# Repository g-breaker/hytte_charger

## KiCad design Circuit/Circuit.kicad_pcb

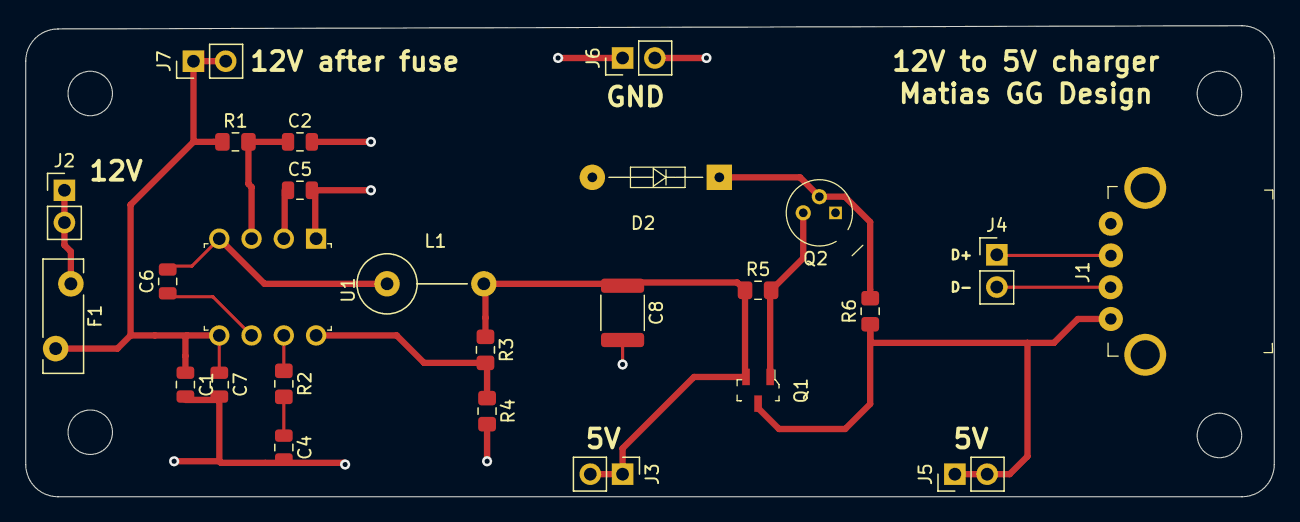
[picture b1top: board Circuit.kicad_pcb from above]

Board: 2 copper layers, 98.3 x 37.1 mm, 30 parts (0 on the bottom side), 16 nets.

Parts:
C1: 220u; C_0805_2012Metric
C2: 2.7n; C_0805_2012Metric
C4: 22n; C_0805_2012Metric
C5, C6, C7: 220n; C_0805_2012Metric
C8: 470u; C_1812_4532Metric
D2: 1N4148; Diode_DO-35_P10mm
F1: Polyfuse; Fuse_Bourns_MF-RHT300
J1: UE27AC54100; USB_A_Female_UE27AC54100
J2, J3, J4, J5, J6, J7: 22-23-2021; PinHeader_1x02_P2.54mm_Vertical
L1: 120u; L_Axial_L11.0mm_D4.5mm_P7.62mm_Vertical_Fastron_MECC
Mnt1, Mnt2, Mnt3, Mnt4: MountingHole_3.5mm
Q1: AO3401A; SOT-23-3
Q2: 2N2222A; TO-18-3
R1: 20k; R_0805_2012Metric_Pad1.15x1.40mm_HandSolder
R2: 9.1k; R_0805_2012Metric_Pad1.15x1.40mm_HandSolder
R3: 1.2k; R_0805_2012Metric_Pad1.15x1.40mm_HandSolder
R4: 2.4k; R_0805_2012Metric_Pad1.15x1.40mm_HandSolder
R5, R6: 10k; R_0805_2012Metric_Pad1.15x1.40mm_HandSolder
U1: L4978; DIP-8_W7.62mm

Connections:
+5V: C8.1, J3.1, J3.2, L1.2, Q1.2, R3.1, R5.1
+12V: F1.1, J2.1, J2.2
/D+: J1.3, J4.1
/D-: J1.2, J4.2
GND: C1.2, C2.2, C4.2, C5.2, C7.2, C8.2, D2.2, J1.4, J6.1, J6.2, Q2.1, R4.2, U1.1
unnamed: C1.1, C7.1, F1.2, J7.1, J7.2, R1.1, U1.5
unnamed: C2.1, R1.2, U1.3
unnamed: C4.1, R2.2
unnamed: C5.1, U1.2
unnamed: C6.1, U1.6
unnamed: C6.2, L1.1, U1.4
unnamed: D2.1, Q2.2, R6.2
unnamed: J1.1, J5.1, J5.2, Q1.3, R6.1
unnamed: Q1.1, Q2.3, R5.2
unnamed: R2.1, U1.7
unnamed: R3.2, R4.1, U1.8

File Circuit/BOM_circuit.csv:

"Id";"Designator";"Package";"Quantity";"Designation";"Supplier and ref";
1;"J7,J5,J6,J4,J3,J2";"PinHeader_1x02_P2.54mm_Vertical";6;"22-23-2021";;;
2;"F1";"Fuse_Bourns_MF-RHT300";1;"Polyfuse";;;
3;"Mnt2,Mnt4,Mnt3,Mnt1";"MountingHole_3.5mm";4;"MountingHole_3.5mm";;;
4;"C8";"C_1812_4532Metric";1;"470u";;;
5;"C7,C6,C5";"C_0805_2012Metric";3;"220n";;;
6;"C4";"C_0805_2012Metric";1;"22n";;;
7;"C2";"C_0805_2012Metric";1;"2.7n";;;
8;"C1";"C_0805_2012Metric";1;"220u";;;
9;"R1";"R_0805_2012Metric_Pad1.15x1.40mm_HandSolder";1;"20k";;;
10;"D2";"Diode_DO-35_P10mm";1;"1N4148";;;
11;"J1";"USB_A_Female_UE27AC54100";1;"UE27AC54100";;;
12;"L1";"L_Axial_L11.0mm_D4.5mm_P7.62mm_Vertical_Fastron_MECC";1;"120u";;;
13;"Q1";"SOT-23-3";1;"AO3401A";;;
14;"Q2";"TO-18-3";1;"2N2222A";;;
15;"R6,R5";"R_0805_2012Metric_Pad1.15x1.40mm_HandSolder";2;"10k";;;
16;"R2";"R_0805_2012Metric_Pad1.15x1.40mm_HandSolder";1;"9.1k";;;
17;"R3";"R_0805_2012Metric_Pad1.15x1.40mm_HandSolder";1;"1.2k";;;
18;"R4";"R_0805_2012Metric_Pad1.15x1.40mm_HandSolder";1;"2.4k";;;
19;"U1";"DIP-8_W7.62mm";1;"L4978";;;

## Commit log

2019-09-10 Soon finnished with PCB
2019-09-10 Finnished PCB
2019-09-11 Added 3D models
2019-09-29 Finnished pcb design, and order PCB
2019-10-08 Final design
2019-10-27 Updated board, shorter board
